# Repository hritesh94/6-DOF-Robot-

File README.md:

# TW2KA 6-DOF Robot Arm — custom PCB, firmware and browser controller 
# Instagram-https://www.instagram.com/zerobudgetbuilds?stkn=Z2p6NzZ4MDZwZGZy&utm_source=ig_contact_invite
# Youtube-https://youtube.com/@zerobudgetbuilds-e4w?si=uFIiYkhq8qUiVjJG

## Here if you see closely the tx and rx connection to the Teensy board is wrong it should be flipped i will correct and upload it in the next iteration

A 3D-printed 6-axis robot arm that homes itself, moves in joint or Cartesian space using inverse kinematics, and **draws** from G-code, SVG files or photos.

> 📹 

https://github.com/user-attachments/assets/a5f0eb35-01ec-4ff1-84e9-ad130a259d0c

## Final Result of What the Robot drew

| | |
|---|---|
| **Mechanics** | Open-source [TW2KA](https://youtube.com/@tw2ka644) arm, 3D-printed on my own printer, assembled and modified |
| **Electronics** | Custom PCB (KiCad): Teensy 4.1 + 6× TMC2209 stepper drivers + 5 endstops |
| **Firmware** | Arduino/Teensyduino, AccelStepper, coordinated moves, homing, EEPROM calibration |
| **Controller** | Single HTML file: live 3D model (three.js), jogging, Cartesian IK, G-code drawing, image → G-code |
| **Status** | Version 1: working and drawing |

---

## What it can do

- **Jog** each joint (press and hold) and **home** J1–J5 on their endstops
- **Cartesian control**: move the tool in X/Y/Z/roll/pitch/yaw, or position-only with the wrist held still
- **Live 3D model** showing the commanded pose and the real motor position side by side
- **Calibrate from the app**: motor direction, homing direction, zero offset, soft limits and steps/degree per joint, all saved on the Teensy
- **Draw**: run G-code (G0/G1/G2/G3, M3/M5), find the reachable drawing area, fit drawings to it, and convert SVG / PNG / JPG images into G-code (outline or hatch)
- **Safety**: E-stop, endstop protection during moves, per-joint speed caps, table-height limit, wrist-flip blocking

## Repository layout

```
6-DOF-Robot-/
├── README.md                          ← you are here
├── LICENSE
├── app/
│   ├── README.md                      ← what the controller does, how to use it
│   ├── tw2k_controller.html           ← the whole controller (open in Chrome/Edge)
│   └── images/                        ← screenshots of the app
├── firmware/
│   └── tw2k_firmware/
│       └── tw2k_firmware.ino          ← Teensy 4.1 firmware
├── hardware/
│   ├── BOM.md                         ← motors, drives, electronics
│   ├── cad/
│   │   ├── README.md                  ← my parts and changes explained
│   │   ├── pen_holder.3mf             ← my pen holder (print-ready)
│   │   ├── pen_holder_preview.png
│   │   ├── Baseplate-v2.3mf           ← modified TW2KA baseplate (inner circle +2 mm)
│   │   ├── baseplate_v2_preview.png
│   │   ├── base_stand_gear_with_lip.3mf  ← modified TW2KA base gear (added lip)
│   │   ├── base_stand_gear_preview.png
│   │   └── Arduino robot arm files + step/   ← original TW2KA design files (credit: TW2KA)
│   │       ├── README.md
│   │       ├── Arm1/  Arm2/  Base/    ← printable parts
│   │       ├── Assembly step.STEP     ← full 3D assembly
│   │       ├── Hardware.txt           ← original hardware list
│   │       └── coupler stl file for planetary geared nema motor.3mf
│   └── pcb/
│       ├── README.md
│       ├── tw2ka_pcb.kicad_pro        ← open this in KiCad
│       ├── tw2ka_pcb.kicad_sch        ← schematic
│       ├── tw2ka_pcb.kicad_pcb        ← 4-layer board layout
│       ├── fp-lib-table
│       ├── 3d/
│       │   └── tw2ka_pcb.step         ← 3D model of the board
│       └── fabrication/               ← drill files (+ Gerbers)
├── docs/
│   ├── 01-build-log.md                ← the story: what I tried, what failed, why each feature exists
│   ├── 02-hardware.md                 ← PCB, pin map, drivers, motors
│   ├── 03-kinematics.md               ← DH parameters, workspace, how the IK works
│   ├── 04-firmware.md                 ← serial protocol, config, EEPROM
│   ├── 05-controller-app.md           ← code map of the HTML app, how to add features
│   ├── 06-calibration.md              ← first-time setup, step by step
│   ├── 07-drawing.md                  ← G-code and image drawing
│   ├── 08-troubleshooting.md          ← problems I hit and how I fixed them
│   └── roadmap.md                     ← ROS 2, MoveIt, camera, learning plans
└── media/                             ← photos and videos
```

## Quick start

1. **Flash the firmware**: open `firmware/tw2k_firmware/tw2k_firmware.ino` in the Arduino IDE with Teensyduino, board **Teensy 4.1**, USB type **Serial**, install **AccelStepper**, upload.
2. **Open the app**: double-click `app/tw2k_controller.html` in **Chrome or Edge** on a computer (Web Serial is needed; phones run it as a simulator only).
3. **Connect → Enable all → Home all.**
4. Follow [docs/06-calibration.md](docs/06-calibration.md) once, then try Cartesian mode and drawing.

⚠️ Keep a hand near STOP (or press **Esc**) and your motor power switch, especially the first time.

## The story in short

1. My first arm used servo motors; I wanted something **precise**.
2. Builders like **Aaed Musa** and **Michael Reeves** inspired me, but precise arms often use BLDC motors with FOC drivers, far over my ₹10–20k budget.
3. **[Skyentific](https://youtube.com/@skyentific)** showed me a precise arm can use **stepper motors**, but his belts aren't sold in India.
4. I found **[TW2KA](https://youtube.com/@tw2ka644)**, and **[Matt.xyz++](https://youtube.com/@matt-04)** showed the same arm writing with G-code (and mentioned TMC drivers). I bought a 3D printer and printed every TW2KA part.
5. TW2KA uses an Arduino Mega + RAMPS + A4988. I moved to a **Teensy 4.1 + TMC2209s**. On a perfboard I killed two drivers and a motor (lesson: never unplug a motor while powered), so I learned **KiCad** and designed my own PCB.
6. Software: the **TW2KA GUI** only jogged the joints, and **Chris Annin's AR4 app** didn't move my arm correctly in X even with my DH parameters. So I **made my own app**.
7. Debugging on the real arm: J3 turning the wrong way, J5's steps per degree, wrist flips, J2 wiring. Then it drew its first SVG.

Full version: [docs/01-build-log.md](docs/01-build-log.md).

## How this was built (honest credits)

- **Mechanical design**: the open-source **TW2KA** arm ([YouTube](https://youtube.com/@tw2ka644)). I printed all parts on my own 3D printer, assembled the arm and modified parts in Fusion 360 (2–3 iterations, plus my own pen holder).
- **PCB**: designed by me in KiCad, soldered and brought up by me (after an earlier perfboard version).
- **Kinematics measurements**: I measured the link geometry axis-to-axis in Fusion 360; the DH table came from those measurements.
- **Software**: the firmware, inverse kinematics and controller app were written with **Claude (Anthropic)** as an AI coding partner, from my requirements, and then tested, debugged and calibrated by me on the real robot.
- **Inspiration and learning**:
  - [Skyentific](https://youtube.com/@skyentific) (stepper-driven 6-axis arm)
  - [Matt.xyz++](https://youtube.com/@matt-04) (TW2KA arm drawing with G-code, TMC drivers)
  - Chris Annin's **AR4** robot and software
  - **Aaed Musa** and **Michael Reeves** (robot builders who got me started)
  - **DIY Engineers** and **Electronoobs** on YouTube (how TMC stepper drivers work)
  - [Inverse kinematics basics playlist](https://www.youtube.com/watch?v=MYJIEiz2DKg&list=PLY6RHB0yqJVasji1rwZAGYirD8zW1ipj-)
- **Libraries**: [AccelStepper](https://www.airspayce.com/mikem/arduino/AccelStepper/) by Mike McCauley, [three.js](https://threejs.org/).

## License

The firmware and app in this repository are released under the MIT License (see `LICENSE`). The TW2KA mechanical design belongs to its creator; check their license before redistributing any of their CAD files.

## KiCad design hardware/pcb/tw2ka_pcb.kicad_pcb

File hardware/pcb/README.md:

# Control PCB (KiCad)

My own control board for the TW2KA arm: a **Teensy 4.1** driving **six TMC2209** stepper drivers, with endstop inputs. Designed in **KiCad 10**.

| | |
|---|---|
| Size | 102 × 100 mm |
| Layers | 4 (F.Cu, In1.Cu, In2.Cu, B.Cu) |
| MCU | Teensy 4.1 (socketed) |
| Drivers | 6 × TMC2209 modules (socketed) |
| Per driver | STEP, DIR, EN to the Teensy; UART RX/TX lines routed (J1–J6_RX/TX); MS1, MS2 and SPREAD selectable |
| Endstops | 5 inputs (SW_1–SW_5) for J1–J5 |
| Power | Motor supply via terminal block and fuse, 100 µF capacitor per driver, separate logic supply (VIO) |

https://github.com/user-attachments/assets/b51a67fe-33f5-430a-8fab-c27dd11908fc

Pin map and endstop wiring: [docs/02-hardware.md](../../docs/02-hardware.md).

## Files

```
hardware/pcb/
├── tw2ka_pcb.kicad_pro     ← open this in KiCad
├── tw2ka_pcb.kicad_sch     ← schematic
├── tw2ka_pcb.kicad_pcb     ← board layout
├── fp-lib-table            ← project footprint library table
├── Tmc2209_pin_socket.pretty/  ← custom TMC2209 socket footprint (to add)
├── 3d/
│   └── tw2ka_pcb.step      ← 3D model of the assembled board
└── fabrication/
    ├── tw2ka_pcb-PTH.drl   ← plated drill file
    ├── tw2ka_pcb-NPTH.drl  ← non-plated drill file
    └── gerbers/            ← Gerber files for the board house (to add)
```

Opening the board works without the footprint libraries (footprints are stored inside the `.kicad_pcb`). To **edit** footprints you also need the `Tmc2209_pin_socket.pretty` folder and the Teensy footprint library (`teensy.pretty`, available on GitHub).

## Ordering the board

Upload the Gerbers and both drill files from `fabrication/` to a PCB manufacturer (JLCPCB, PCBWay, etc.) and choose **4 layers**.

## Lessons from the perfboard version

- Put a 100 µF capacitor rated **35 V** (not 25 V) on each driver's motor supply.
- **Never plug or unplug a motor while the driver is powered.** It can destroy a TMC2209, which is how I lost two drivers and a motor.

## Next revision

- [ ] [Describe the small tweak you want to make]

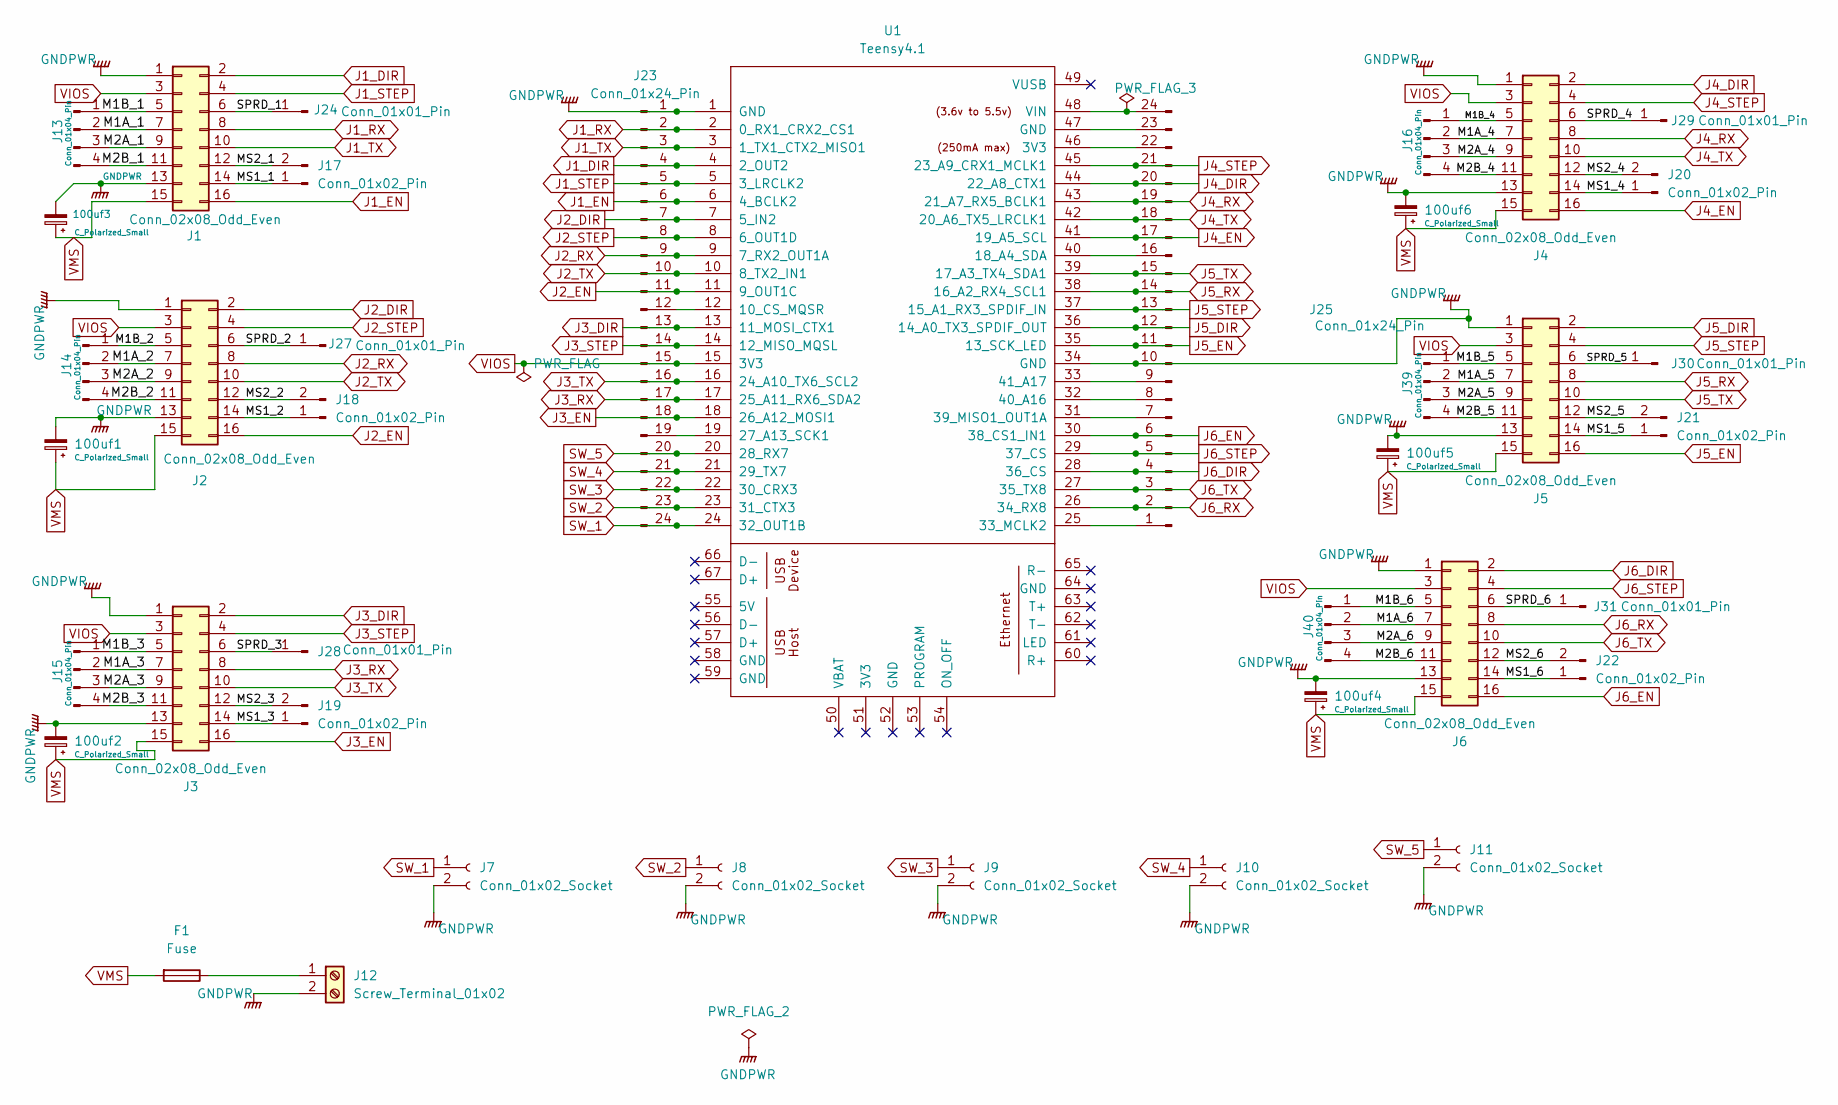
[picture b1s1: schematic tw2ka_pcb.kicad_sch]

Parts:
100uf1, 100uf2, 100uf3, 100uf4, 100uf5, 100uf6: C_Polarized_Small; CP_Elec_6.3x7.7
F1: Fuse; Fuseholder_Cylinder-5x20mm_Schurter_0031_8201_Horizontal_Op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
J1, J2, J3, J4, J5, J6: Conn_02x08_Odd_Even; TMC2209_MODULE
J7, J8, J9, J10, J11: Conn_01x02_Socket; PinHeader_1x02_P2.54mm_Vertical
J12: Screw_Terminal_01x02; TerminalBlock_Phoenix_MKDS-1,5-2-5.08_1x02_P5.08mm_Horizont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
J13, J14, J15, J16, J39, J40: Conn_01x04_Pin; PinHeader_1x04_P2.54mm_Vertical
J17, J18, J19, J20, J21, J22: Conn_01x02_Pin; PinHeader_1x02_P2.54mm_Vertical
J23, J25: Conn_01x24_Pin; PinHeader_1x24_P2.54mm_Vertical
J24, J27, J28, J29, J30, J31: Conn_01x01_Pin; PinHeader_1x01_P2.54mm_Vertical
U1: Teensy4.1; Teensy41

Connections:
/M1A_1: J1.7, J13.2
/M1A_2: J2.7, J14.2
/M1A_3: J3.7, J15.2
/M1A_4: J4.7, J16.2
/M1A_5: J5.7, J39.2
/M1A_6: J6.7, J40.2
/M1B_1: J1.5, J13.1
/M1B_2: J2.5, J14.1
/M1B_3: J3.5, J15.1
/M1B_4: J4.5, J16.1
/M1B_5: J5.5, J39.1
/M1B_6: J6.5, J40.1
/M2A_1: J1.9, J13.3
/M2A_2: J2.9, J14.3
/M2A_3: J3.9, J15.3
/M2A_4: J4.9, J16.3
/M2A_5: J5.9, J39.3
/M2A_6: J6.9, J40.3
/M2B_1: J1.11, J13.4
/M2B_2: J2.11, J14.4
/M2B_3: J3.11, J15.4
/M2B_4: J4.11, J16.4
/M2B_5: J5.11, J39.4
/M2B_6: J6.11, J40.4
/MS1_1: J1.14, J17.1
/MS1_2: J2.14, J18.1
/MS1_3: J3.14, J19.1
/MS1_4: J4.14, J20.1
/MS1_5: J5.14, J21.1
/MS1_6: J6.14, J22.1
/MS2_1: J1.12, J17.2
/MS2_2: J2.12, J18.2
/MS2_3: J3.12, J19.2
/MS2_4: J4.12, J20.2
/MS2_5: J5.12, J21.2
/MS2_6: J6.12, J22.2
/SPRD_1: J1.6, J24.1 (Pin_1_1)
/SPRD_2: J2.6, J27.1 (Pin_1_1)
/SPRD_3: J3.6, J28.1 (Pin_1_1)
/SPRD_4: J4.6, J29.1 (Pin_1_1)
/SPRD_5: J5.6, J30.1 (Pin_1_1)
/SPRD_6: J6.6, J31.1 (Pin_1_1)
GNDPWR: 100uf1.2, 100uf2.2, 100uf3.2, 100uf4.2, 100uf5.2, 100uf6.2, J1.1, J1.13, J2.1, J2.13, J3.1, J3.13, J4.1, J4.13, J5.1, J5.13, J6.1, J6.13, J7.2, J8.2, J9.2, J10.2, J11.2, J12.2, J23.1, J25.10, U1.1 (GND), U1.34 (GND)
J1_DIR: J1.2, J23.4, U1.4 (2_OUT2)
J1_EN: J1.16, J23.6, U1.6 (4_BCLK2)
J1_RX: J1.8, J23.2, U1.2 (0_RX1_CRX2_CS1)
J1_STEP: J1.4, J23.5, U1.5 (3_LRCLK2)
J1_TX: J1.10, J23.3, U1.3 (1_TX1_CTX2_MISO1)
J2_DIR: J2.2, J23.7, U1.7 (5_IN2)
J2_EN: J2.16, J23.11, U1.11 (9_OUT1C)
J2_RX: J2.8, J23.9, U1.9 (7_RX2_OUT1A)
J2_STEP: J2.4, J23.8, U1.8 (6_OUT1D)
J2_TX: J2.10, J23.10, U1.10 (8_TX2_IN1)
J3_DIR: J3.2, J23.13, U1.13 (11_MOSI_CTX1)
J3_EN: J3.16, J23.18, U1.18 (26_A12_MOSI1)
J3_RX: J3.8, J23.17, U1.17 (25_A11_RX6_SDA2)
J3_STEP: J3.4, J23.14, U1.14 (12_MISO_MQSL)
J3_TX: J3.10, J23.16, U1.16 (24_A10_TX6_SCL2)
J4_DIR: J4.2, J25.20, U1.44 (22_A8_CTX1)
J4_EN: J4.16, J25.17, U1.41 (19_A5_SCL)
J4_RX: J4.8, J25.19, U1.43 (21_A7_RX5_BCLK1)
J4_STEP: J4.4, J25.21, U1.45 (23_A9_CRX1_MCLK1)
J4_TX: J4.10, J25.18, U1.42 (20_A6_TX5_LRCLK1)
J5_DIR: J5.2, J25.12, U1.36 (14_A0_TX3_SPDIF_OUT)
J5_EN: J5.16, J25.11, U1.35 (13_SCK_LED)
J5_RX: J5.8, J25.14, U1.38 (16_A2_RX4_SCL1)
J5_STEP: J5.4, J25.13, U1.37 (15_A1_RX3_SPDIF_IN)
J5_TX: J5.10, J25.15, U1.39 (17_A3_TX4_SDA1)
J6_DIR: J6.2, J25.4, U1.28 (36_CS)
J6_EN: J6.16, J25.6, U1.30 (38_CS1_IN1)
J6_RX: J6.8, J25.2, U1.26 (34_RX8)
J6_STEP: J6.4, J25.5, U1.29 (37_CS)
J6_TX: J6.10, J25.3, U1.27 (35_TX8)
unnamed: F1.1, J12.1
unnamed: J23.12, U1.12 (10_CS_MQSR)
unnamed: J23.19, U1.19 (27_A13_SCK1)
unnamed: J25.1, U1.25 (33_MCLK2)
unnamed: J25.7, U1.31 (39_MISO1_OUT1A)
unnamed: J25.8, U1.32 (40_A16)
unnamed: J25.9, U1.33 (41_A17)
unnamed: J25.16, U1.40 (18_A4_SDA)
unnamed: J25.22, U1.46 (3V3)
unnamed: J25.23, U1.47 (GND)
unnamed: J25.24, U1.48 (VIN)
SW_1: J7.1, J23.24, U1.24 (32_OUT1B)
SW_2: J8.1, J23.23, U1.23 (31_CTX3)
SW_3: J9.1, J23.22, U1.22 (30_CRX3)
SW_4: J10.1, J23.21, U1.21 (29_TX7)
SW_5: J11.1, J23.20, U1.20 (28_RX7)
VIOS: J1.3, J2.3, J3.3, J4.3, J5.3, J6.3, J23.15, U1.15 (3V3)
VMS: 100uf1.1, 100uf2.1, 100uf3.1, 100uf4.1, 100uf5.1, 100uf6.1, F1.2, J1.15, J2.15, J3.15, J4.15, J5.15, J6.15

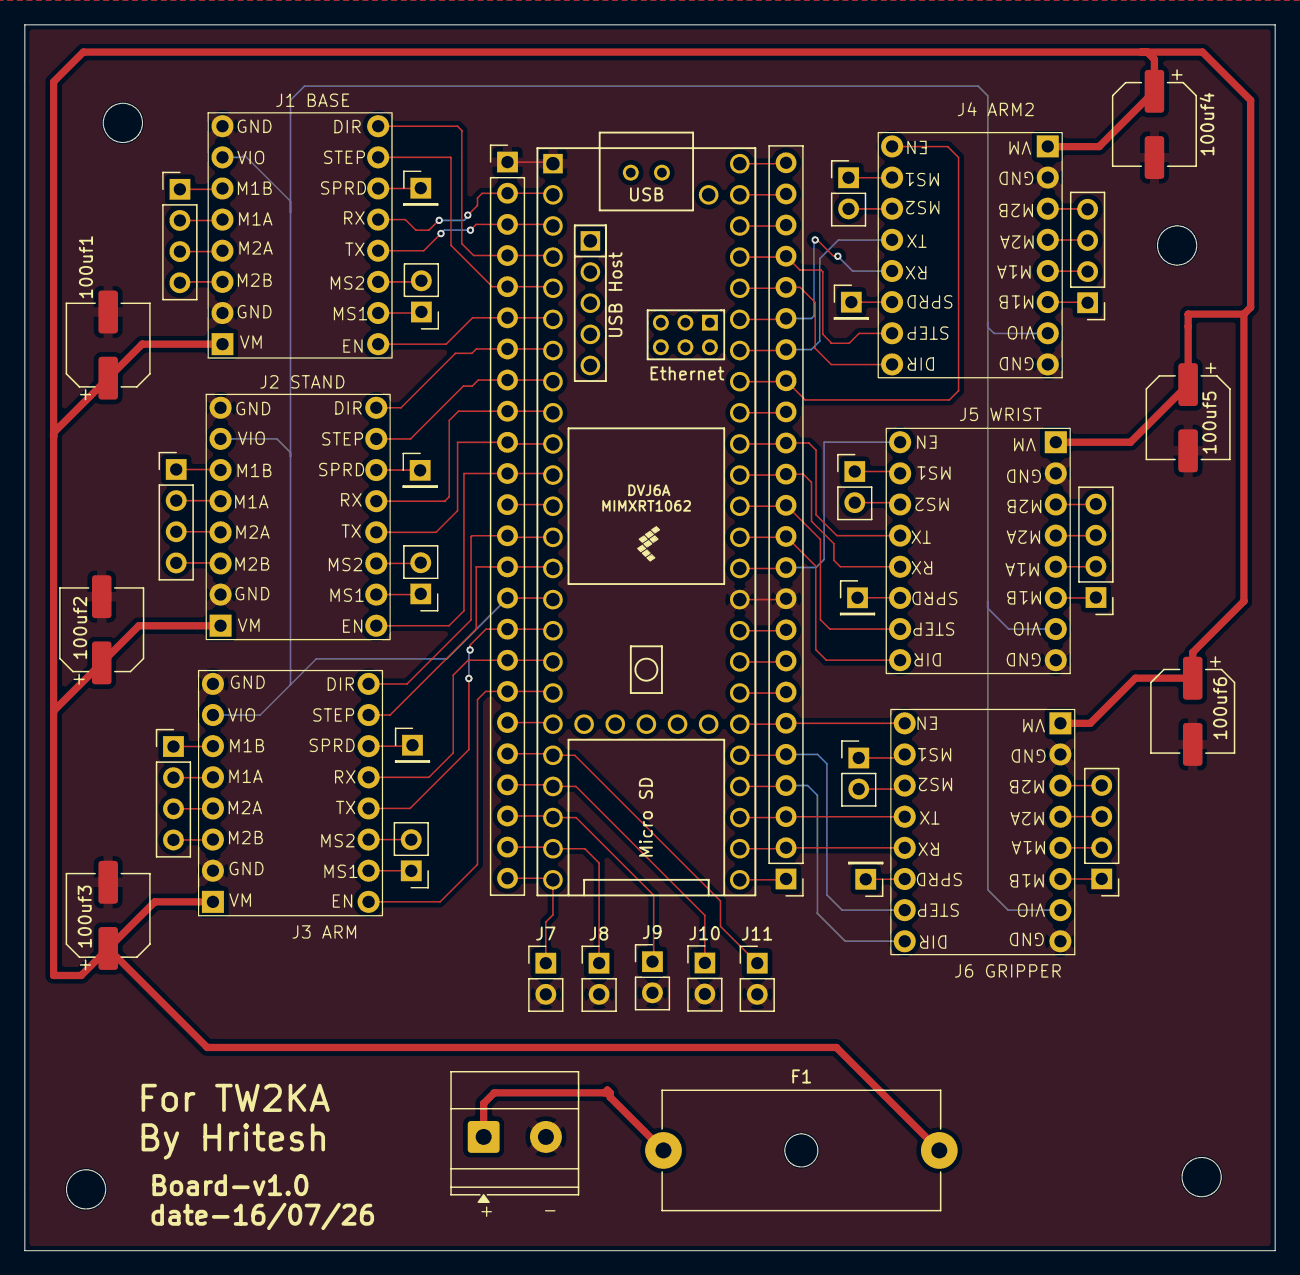
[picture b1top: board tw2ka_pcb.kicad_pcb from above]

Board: 4 copper layers, 102.0 x 100.0 mm, 40 parts (0 on the bottom side), 91 nets.
